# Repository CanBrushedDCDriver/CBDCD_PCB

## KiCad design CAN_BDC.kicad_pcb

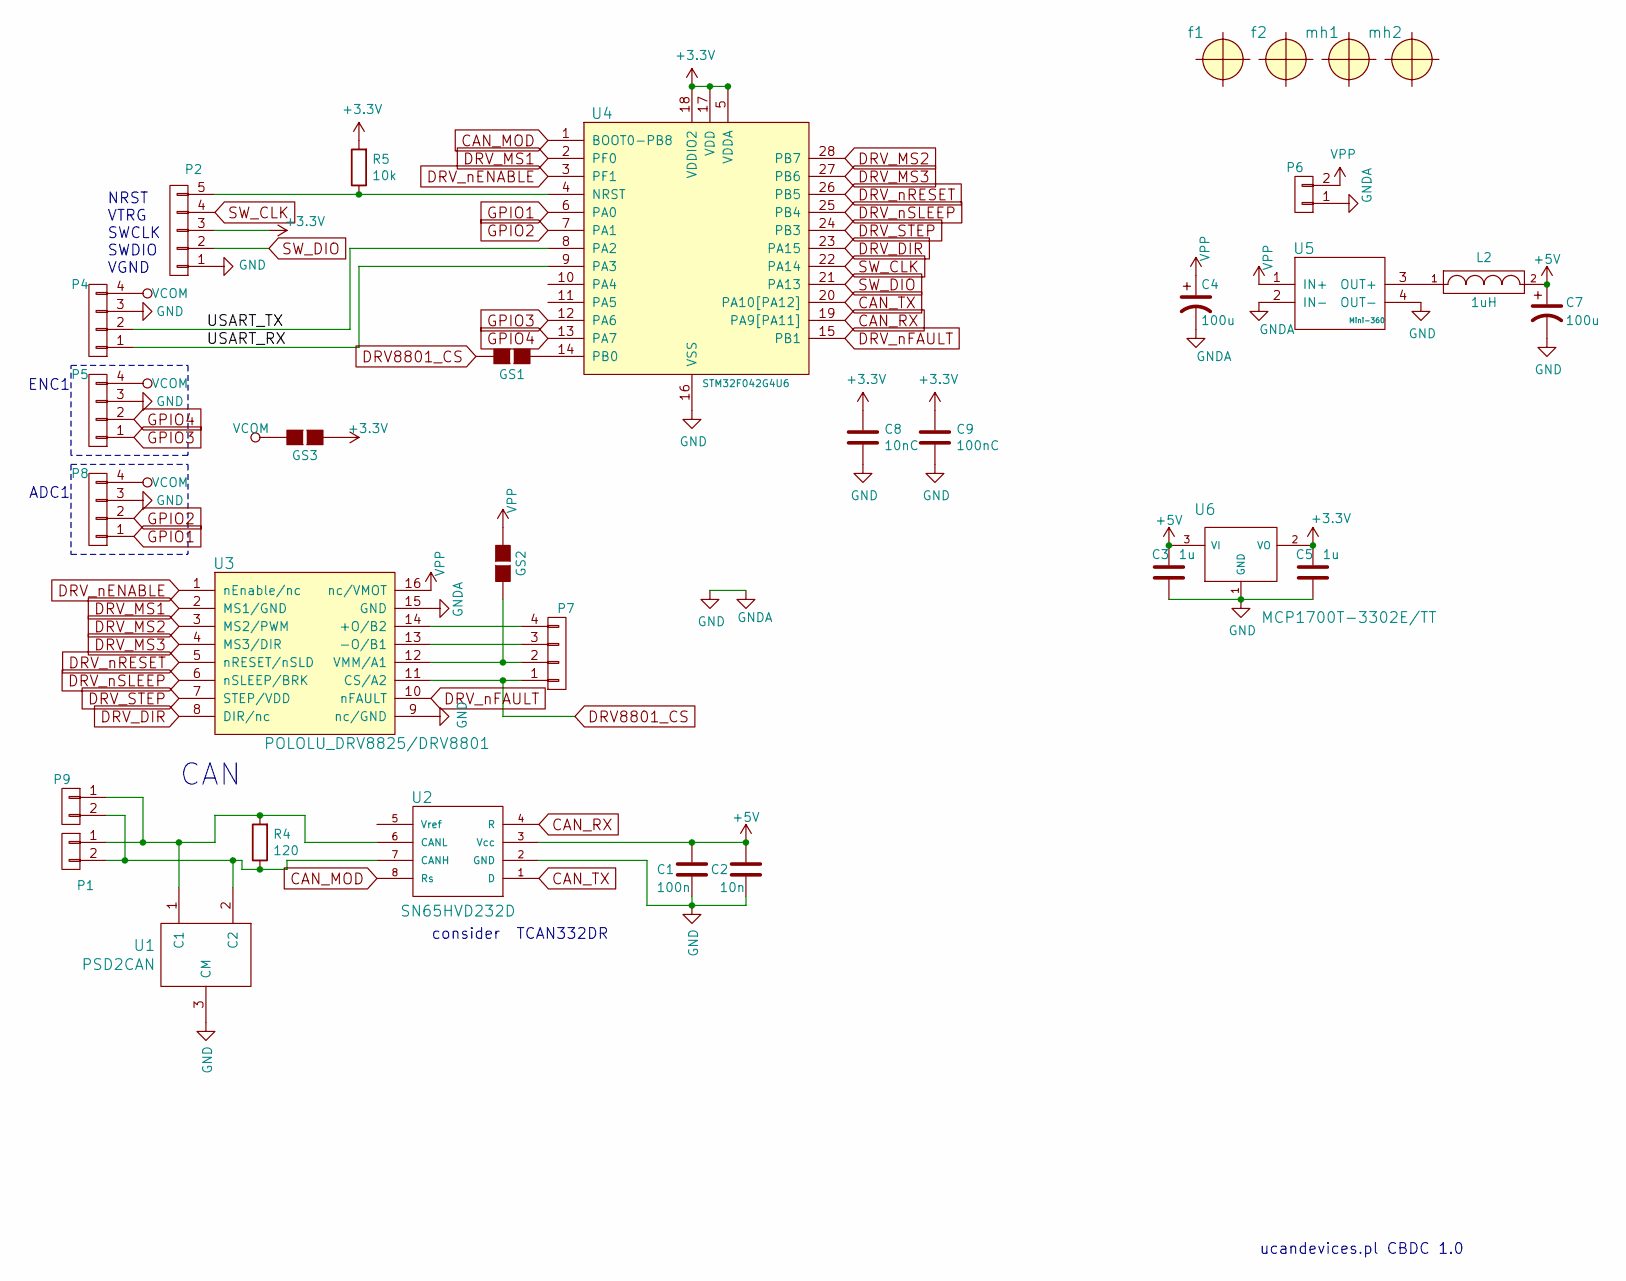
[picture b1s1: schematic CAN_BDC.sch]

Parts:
C1: 100n; C_0402
C2: 10n; C_0402
C3, C5: 1u; C_0402
C4: 100u; c_elec_6.3x5.3
C7: 100u; c_elec_5x5.8
C8: 10nC; C_0402
C9: 100nC; C_0402
GS1, GS2, GS3: GS2
L2: 1uH; C_1206
P1, P9: CONN_01X02; Pin_Header_Straight_1x02_Pitch2.54mm
P2: CONN_01X05; Pin_Header_Straight_1x05_Pitch1.27mm_SMD_Pin1Left
P4, P5, P8: CONN_01X04; Pin_Header_Straight_1x04_Pitch2.54mm
P6: CONN_01X02; TerminalBlock_Pheonix_MPT-2.54mm_2pol
P7: CONN_01X04; TerminalBlock_Pheonix_MPT-2.54mm_4pol
R4: 120; R_0603
R5: 10k; R_0402
U1: PSD2CAN; SOT-23; MFG Part Num PESD2CAN.215
U2: SN65HVD232D; SO; MFG Part Num SN65HVD232D
U3: POLOLU_DRV8825/DRV8801
U4: STM32F042G4U6; UFQFPN_28; MFG Part Num STM32F042G4U6
U5: Mini-360
U6: MCP1700T-3302E/TT; SOT-23
f1, f2: fiducial; Fiducial_1mm_Dia_2.54mm_Outer_CopperTop
mh1, mh2: fiducial; 1pin

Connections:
+3V3: C5.1, C8.1, C9.1, GS3.1 (G1), P2.3, R5.2, U4.5 (VDDA), U4.17 (VDD), U4.18 (VDDIO2), U6.2 (VO)
+5V: C1.1, C2.1, C3.1, C7.1, L2.2, U2.3 (Vcc), U6.3 (VI)
/USART_RX: P4.1, U4.9 (PA3)
/USART_TX: P4.2, U4.8 (PA2)
CAN_MOD: U2.8 (Rs), U4.1 (BOOT0-PB8)
CAN_RX: U2.4 (R), U4.19 (PA9[PA11])
CAN_TX: U2.1 (D), U4.20 (PA10[PA12])
DRV8801_CS: GS1.2 (G2), P7.1, U3.11 (CS/A2)
DRV_DIR: U3.8 (DIR/nc), U4.23 (PA15)
DRV_MS1: U3.2 (MS1/GND), U4.2 (PF0)
DRV_MS2: U3.3 (MS2/PWM), U4.28 (PB7)
DRV_MS3: U3.4 (MS3/DIR), U4.27 (PB6)
DRV_STEP: U3.7 (STEP/VDD), U4.24 (PB3)
DRV_nENABLE: U3.1 (nEnable/nc), U4.3 (PF1)
DRV_nFAULT: U3.10 (nFAULT), U4.15 (PB1)
DRV_nRESET: U3.5 (nRESET/nSLD), U4.26 (PB5)
DRV_nSLEEP: U3.6 (nSLEEP/BRK), U4.25 (PB4)
GND: C1.2, C2.2, C3.2, C4.2, C5.2, C7.2, C8.2, C9.2, P2.1, P4.3, P5.3, P6.1, P8.3, U1.3 (CM), U2.2 (GND), U3.9 (nc/GND), U3.15 (GND), U4.16 (VSS), U5.2 (IN-), U5.4 (OUT-), U6.1 (GND), mh1.1, mh2.1
GPIO1: P8.1, U4.6 (PA0)
GPIO2: P8.2, U4.7 (PA1)
GPIO3: P5.1, U4.12 (PA6)
GPIO4: P5.2, U4.13 (PA7)
unnamed: GS1.1 (G1), U4.14 (PB0)
unnamed: GS2.2 (G2), P7.2, U3.12 (VMM/A1)
unnamed: L2.1, U5.3 (OUT+)
unnamed: P1.1, P9.1, R4.2, U1.1 (C1), U2.6 (CANL)
unnamed: P1.2, P9.2, R4.1, U1.2 (C2), U2.7 (CANH)
unnamed: P2.5, R5.1, U4.4 (NRST)
unnamed: P7.3, U3.13 (-O/B1)
unnamed: P7.4, U3.14 (+O/B2)
SW_CLK: P2.4, U4.22 (PA14)
SW_DIO: P2.2, U4.21 (PA13)
VCOM: GS3.2 (G2), P4.4, P5.4, P8.4
VPP: C4.1, GS2.1 (G1), P6.2, U3.16 (nc/VMOT), U5.1 (IN+)

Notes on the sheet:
NRST VTRG SWCLK SWDIO VGND
CAN
ucandevices.pl CBDC 1.0
ENC1
consider TCAN332DR
ADC1

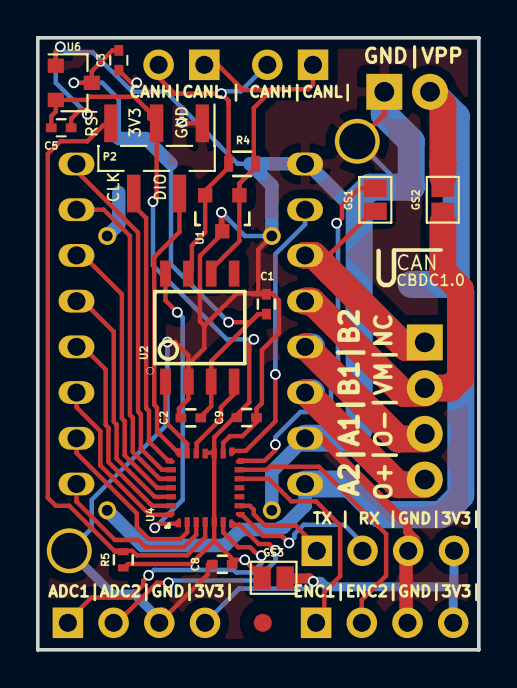
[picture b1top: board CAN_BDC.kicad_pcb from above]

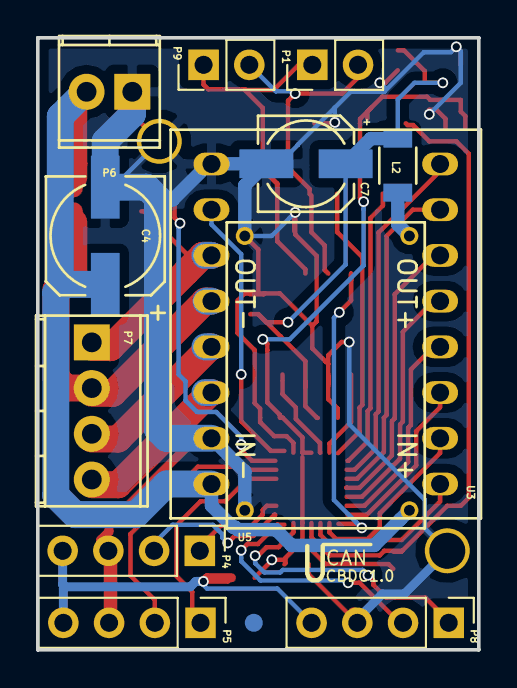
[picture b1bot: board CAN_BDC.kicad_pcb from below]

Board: 2 copper layers, 24.5 x 34.0 mm, 32 parts (13 on the bottom side), 34 nets.

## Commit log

2016-10-10 Initial Commit
    Initial Commit
2016-10-10 Footpritns addition.
    Footpritns addition.
2016-10-10 Layout Creation
    Layout Creation
2016-10-11 Outline update
2016-10-11 Connector update
2016-10-15 DRV8834 Addition
    DRV8834 Addition
2016-10-17 DRV8834 board update
    DRV8834 board update
2016-10-18 Pcb wirring 1
2016-10-19 Tracks Placement Motor
    Tracks Placement Motor
2016-10-20 POLOLU_Stepper driver addition
    POLOLU_Stepper driver addition
2016-10-21 buck converter addition
    buck converter addition
2016-10-22 step up converter routing
2016-10-24 Footprints update
    Footprints update
2016-10-24 Buck Converter Layout update.
2016-10-24 Layout improve
2016-10-26 Bootconnector addition
2016-10-27 Fids addition
2016-10-28 Footprint update.
2016-10-28 Root full
    Root full
2016-10-29 Gerber generation
2016-10-31 Gerber Update.
2017-01-02 Buck-converter update.
    Buck-converter update.
2017-01-11 Connector Footprint update
    Connector Footprint update
2017-01-12 Ninigi footprint addition
    Ninigi footprint addition
2017-01-12 Layout update
2017-01-13 Tracks update
2017-01-14 DRV8825 and DRV8801 solder pads addition
2017-01-16 Full root
2017-01-16 Connector reposition
2017-01-16 CAN layout update
2017-01-25 Mini-360 Flip
2017-01-25 Resistor footprint update
2017-01-26 ZL321 Footprint add
2017-01-27 Description add
2017-01-31 Init
2017-02-01 Layout 1
2017-02-02 Capacitors Addition
2017-02-02 layout 2
2017-02-03 Layout 3
2017-02-03 Route
2017-02-04 Desc update
2017-02-06 Motor singlas update
2017-02-09 Output files
2017-02-13 Size reduction
2017-02-13 regulator addition
2017-02-14 Capacitor placment update
2017-02-14 Gerber Files generation
2017-02-16 Solder jumper addtion
